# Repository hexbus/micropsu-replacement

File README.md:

# micropsu-replacement
This 1.0c version is a drop-in replacement for a ±12V and +5V micro power supply, requiring minimal soldering.

## Specifications:

**Input:** Max 4A @ 12V regulated (use a high-quality supply) via J1 (wires) or J3 (barrel input).

**Output:** +5V @ 3A (with DFR8031 slightly de-rated for heat dissipation), -12V @ 1A, and the remaining capacity to the 12V input via J2's four pin output.

While you **might** be able to exceed more than a total of 4A output by providing more than 4A input (i.e. 6A, so you can pull more than 12V from the 12V rail), it’s untested and unadvised — **you are on your own - proceed with extreme caution**.

## Background:

This board is primarily designed for various low-voltage retro computer systems and peripherals needing tri-voltage output (+5V, -12V, +12V), such as MSX systems, the Commodore Amiga, RS232 interfaces, the Corcomp 9900 sidecar, and other perhipherals that needed tri-voltage power supplies.  

### Latest Changes: 

Changes with 1.0c of the board is slightly more compact, has holes in it for mounting, and has a barrel 12V input option.  You may use the 12V J1 input OR the barrel 12V input.  DO NOT use both!

## Thanks: 

This board a remix of [dabonetn's TI-99/4A replacement power supply project](https://github.com/dabonetn/ti99psu-replacement), which is based on jonn-reenthused's [TI99-4A-dc-power-board](https://github.com/jonn-reenthused/TI99-4A-dc-power-board). I’ve ported it from EasyEDA to KiCAD, but still haven't figured out the schematic part of KiCAD yet.  Please feel free to offer any merges with added schematics. Thanks to both authors for keeping these systems alive, and to members of the Atlanta Historic Computing Society for supporting and offering feedback on this project.

### Original author notes (adapted for my board):

* 5V: This uses a DFR0831 5v buck converter, that's rated for +5v@4a, but I recommned no more than 3.5a draw.  You should also use a 2.5mm thermal pad underneath the DFR8031 to help cool it.
* -12V: -12v is provided with a P78E12-1000 switching regulator
* 12V:  Provided by a regulated 12V power supply.  Use a good one for input.  Do not exceed the cumulative 4A input.
* Use the recommended 560ohm resistor for a bright LED or 2.2k for a dull LED.
* The SUP53P06-20-E3 mosfet is there for reverse voltage input, but you can leave it out by connecting pins d & s ( the two close to the edge of the board)

## BOM:
(Links lead to Mouser, but many items are much less expensive on Aliexpress, 14 items total):

* SW1:  [500SDP1S1M2QEA](https://www.mouser.com/ProductDetail/E-Switch/500SDP1S1M2QEA?qs=%252BZnE%2FxbLNR9K23nY3Tws9g%3D%3D) E-Switch DPDT, 4A minimum, PC-PIN or equivalent 
* J1: 	[09652028](https://www.mouser.com/ProductDetail/Molex/09-65-2028?qs=sGAEpiMZZMvlX3nhDDO4AMj2eUq01hUX%252BAhYX12ZlRg%3D) 2-pin 3.96 Molex
* J2:	[26604040](https://www.mouser.com/ProductDetail/Molex/26-60-4040?qs=tRPrwvvr%2FuiQpDQcO3P3Lw%3D%3D) 4-pin 3.96 Molex
* J3:	[WE 694106301002](https://www.mouser.com/ProductDetail/Wurth-Elektronik/694106301002?qs=a9WhcLg8qCwOEkcI62k5mA%3D%3D) DC Barrel connector 2.5/2.1MM
* Q1:	[FQP47P06](https://www.mouser.com/ProductDetail/onsemi-Fairchild/FQP47P06?qs=ZS9em9a1DI4QoVAAU1ygLw%3D%3D) Mosfet for reverse protection - also, much cheaper in bulk on Aliexpress.
* R1:	[560 ohm 1/4 resistor](https://www.mouser.com/ProductDetail/YAGEO/CFR-25JT-52-560R?qs=sGAEpiMZZMsPqMdJzcrNwslF2s3r2P4uPdiIn5eV7%252BI%3D)
* [DFR0831](https://www.mouser.com/ProductDetail/DFRobot/DFR0831?qs=iLbezkQI%252BsjsPFkttXQbEA%3D%3D): 30 and lower to 5V step down, 4A.  Also known as "Mini 560". Highly suggest a thermal pad between the back of this and the board.
* LED1: Regular LED (any kind, color)
* Capacitors: (2) [10uf, 25V](https://www.mouser.com/ProductDetail/667-ECA-1EM100), 2.0mm lead spacing, (3) [22uf, 16v](https://www.mouser.com/ProductDetail/667-ECE-A1EKA220), 2.0mm spacing
* VR1: 	(Not marked):  -12V P78E12-1000 DC-DC converter or [LM7912](https://www.mouser.com/ProductDetail/Texas-Instruments/LM7912CT-NOPB?qs=QbsRYf82W3GCP0%2FQjKEJfQ%3D%3D) 1A -12V converter.  Please Note:  CUI is working on a successor to the P78E12-1000.  The current recommended replacement does NOT support negative voltage.

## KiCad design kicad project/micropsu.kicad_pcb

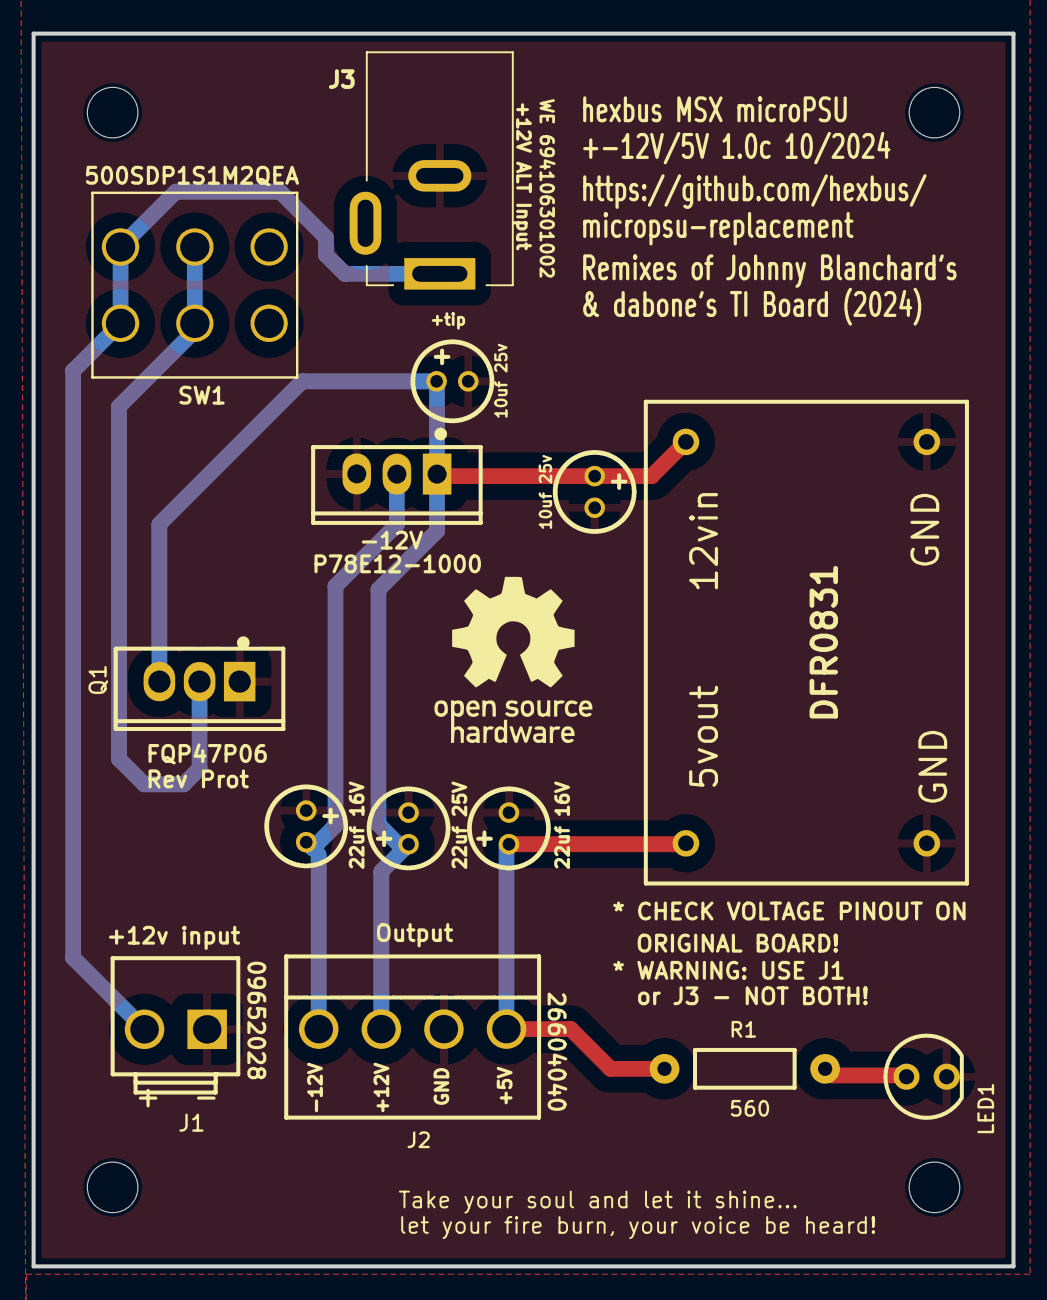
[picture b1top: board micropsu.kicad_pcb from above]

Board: 2 copper layers, 62.0 x 78.0 mm, 14 parts (0 on the bottom side), 5 nets.

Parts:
+5INPUT, +12OUTPUT: 10uf 25v; CAP-D5.0×F2.0
+5OUTPUT: 22uf 16v; CAP-D5.0×F2.0
+12V ALT Input: BarrelJack_Kycon_KLDX-0202-xC_Horizontal
-5INPUT: 10uf 25v; CAP-D5.0×F2.0
-5OUTPUT: 22uf 16v; CAP-D5.0×F2.0
J1: B2P-VH-BL(LF)(SN); CONN-TH-2P-P3.96_B2P-VH-BL-LF-SN
J2: Header-Male-2.54_1x4; DIP-1X4P-3.96MM-SK
LED1: LED-5MM; LED-5MM/2.54
P78E12-1000: VXO7805-1000; TO-220-3_L10.0-W4.5-P2.54-L
Q1: FQP47P06; TO-220F-3_L10.2-W4.9-P2.54-L
R1: 560; L_AXIAL-0.4
SW1: 500SDP1S1M2QEA; SW6_M2QEA_EWI
U3: dfr0831V2; DFR0831FOOT

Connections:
+5V: +5OUTPUT.1, J2.4, R1.1, U3.4
+12V: +5INPUT.1, +12OUTPUT.1, +12V ALT Input.1, -5INPUT.1, J1.2, J2.2, P78E12-1000.1, Q1.2, Q1.3, SW1.1, SW1.2, SW1.5, SW1.6, U3.2
-12V: -5OUTPUT.2, J2.1, P78E12-1000.2
GND: +5INPUT.2, +5OUTPUT.2, +12OUTPUT.2, +12V ALT Input.2, -5INPUT.2, -5OUTPUT.1, J1.1, J2.3, LED1.2, P78E12-1000.3, Q1.1, U3.1, U3.3
LED1_1: LED1.1, R1.2

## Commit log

2024-09-20 Update README.md
    Changed to my version
2024-09-20 Delete Easyeda directory
    Removing old project
2024-09-20 Initial uploads
2024-09-20 Create LICENSE
    Adding GPL v3.0 license
2024-09-20 Adding zip file for 1.0b gerbers
2024-10-15 updated version of board
2024-10-15 adding new files for new version
2024-10-15 fixed readme
2024-10-15 resized picture
2024-10-15 updated to v1.0c and resized images and changed directory structure
2024-10-15 same as last time
2024-10-15 fixed file extension
2025-04-10 Delete LICENSE
    changing to MIT license
2025-04-10 Create LICENSE
